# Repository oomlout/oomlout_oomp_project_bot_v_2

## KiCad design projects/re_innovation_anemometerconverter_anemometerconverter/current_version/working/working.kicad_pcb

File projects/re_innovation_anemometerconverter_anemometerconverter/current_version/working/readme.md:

# anemometerconverter
 
## summary 
* id: re_innovation_anemometerconverter_anemometerconverter
* user: re_innovation
* name: anemometerconverter
* board: anemometerconverter
* repo: https://github.com/re-innovation/AnemometerConverter
* src_file_repo_kicad_pcb: AnemometerConverter_PCB/AnemometerConverter.kicad_pcb
* src_file_repo_kicad_pcb_link: https://github.com/re-innovation/AnemometerConverter/tree/master/AnemometerConverter_PCB/AnemometerConverter.kicad_pcb

* src_file_repo_sch: AnemometerConverter_PCB/AnemometerConverter.sch
* src_file_repo_sch_link: https://github.com/re-innovation/AnemometerConverter/tree/master/AnemometerConverter_PCB/AnemometerConverter.sch
* full details link: https://github.com/oomlout/oomlout_oomp_project_bot_v_2/tree/main/projects/re_innovation_anemometerconverter_anemometerconverter/current_version/working

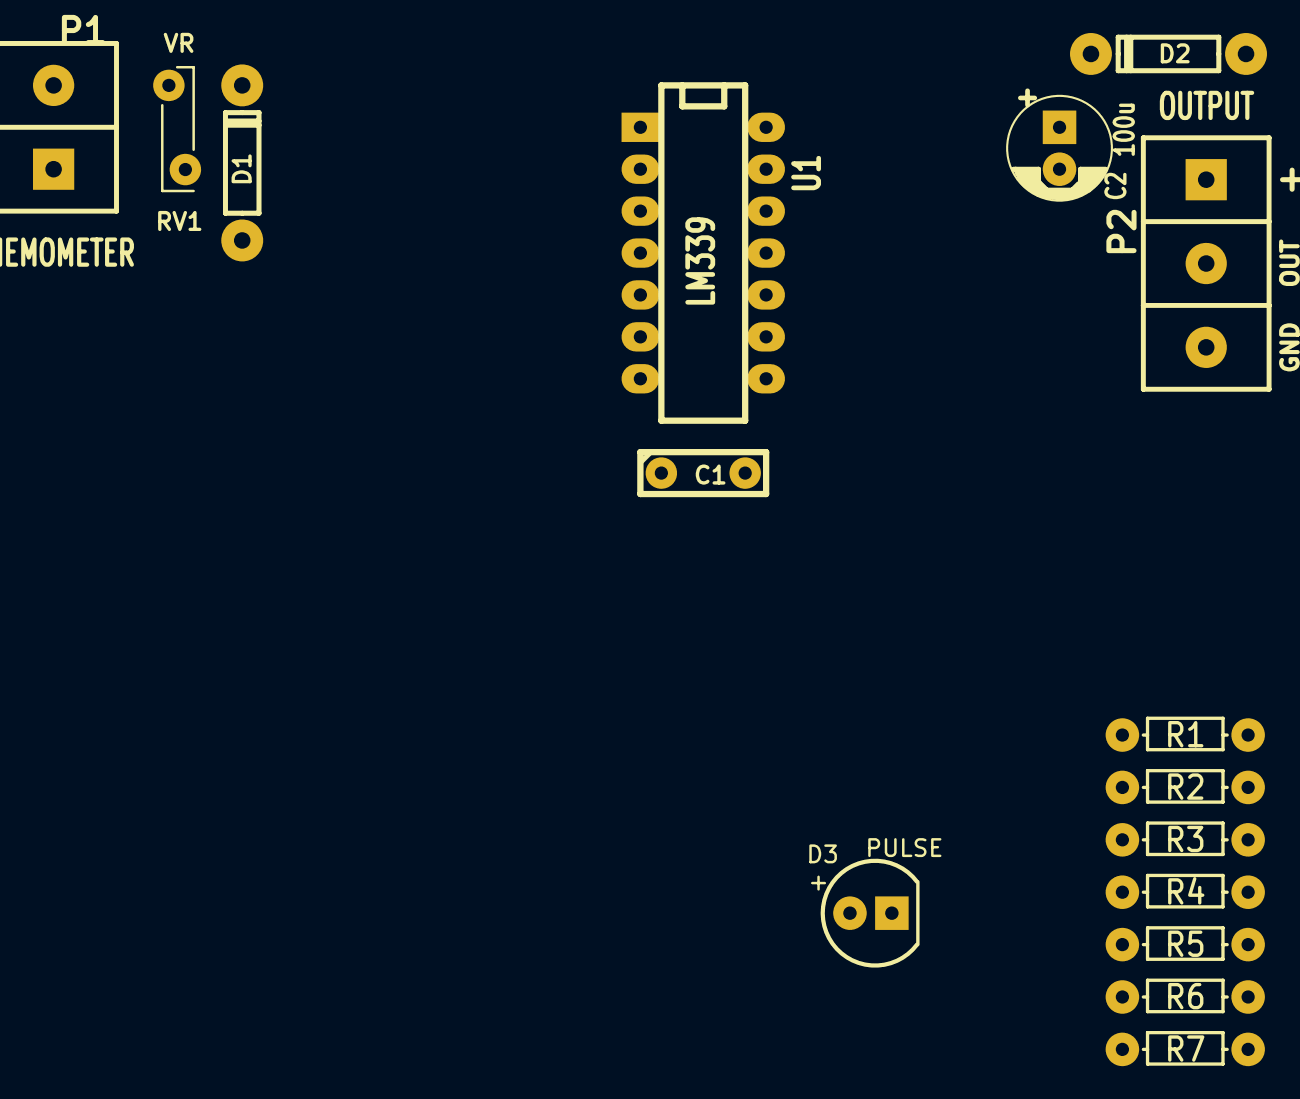
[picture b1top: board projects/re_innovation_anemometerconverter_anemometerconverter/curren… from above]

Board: 2 copper layers, 16 parts (0 on the bottom side), 9 nets, no tracks yet.

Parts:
C1: 22n; C1_wide_lg_pad
C2: 100u; C_1V7_TH
D1: 1N914; TH_Diode_1
D2: 1N4001; TH_Diode_1
D3: PULSE; TH_LED-5MM_larg_pad
P1: ANEMOMETER; SIL-2_screw_terminal
P2: OUTPUT; SIL-3_screw_terminal
R1, R2: 4k7; TH_Resistor_1
R3, R4: 100k; TH_Resistor_1
R5: 10k; TH_Resistor_1
R6: 4M7; TH_Resistor_1
R7: 1k; TH_Resistor_1
RV1: VR; TH_MC36188_FUSE
U1: LM339; DIP-14__300_ELL_lg_pad

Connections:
GND: C1.2, C2.2, D1.2, P1.1, P2.3, R5.2, R7.2, RV1.2, U1.12
unnamed: C1.1, R2.1, R3.2, U1.4
unnamed: D1.1, R1.1, R2.2
unnamed: D2.2, P2.1
unnamed: D3.1, R7.1
unnamed: D3.2, P2.2, R6.1, U1.2
unnamed: P1.2, R1.2, RV1.1
unnamed: R4.2, R5.1, R6.2, U1.5
VCC: C2.1, D2.1, R3.1, R4.1, U1.3

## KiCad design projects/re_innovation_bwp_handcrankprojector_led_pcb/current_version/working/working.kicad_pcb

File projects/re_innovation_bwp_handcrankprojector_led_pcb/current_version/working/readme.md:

# bwp
 
## summary 
* id: re_innovation_bwp_handcrankprojector_led_pcb
* user: re_innovation
* name: bwp
* board: handcrankprojector_led_pcb
* repo: https://github.com/re-innovation/bwp
* src_file_repo_kicad_pcb: Projection_Unit_PCB/LED_Unit_PCB/HandCrankProjector_LED_PCB.kicad_pcb
* src_file_repo_kicad_pcb_link: https://github.com/re-innovation/bwp/tree/master/Projection_Unit_PCB/LED_Unit_PCB/HandCrankProjector_LED_PCB.kicad_pcb

* src_file_repo_sch: Projection_Unit_PCB/LED_Unit_PCB/HandCrankProjector_LED_PCB.sch
* src_file_repo_sch_link: https://github.com/re-innovation/bwp/tree/master/Projection_Unit_PCB/LED_Unit_PCB/HandCrankProjector_LED_PCB.sch
* full details link: https://github.com/oomlout/oomlout_oomp_project_bot_v_2/tree/main/projects/re_innovation_bwp_handcrankprojector_led_pcb/current_version/working

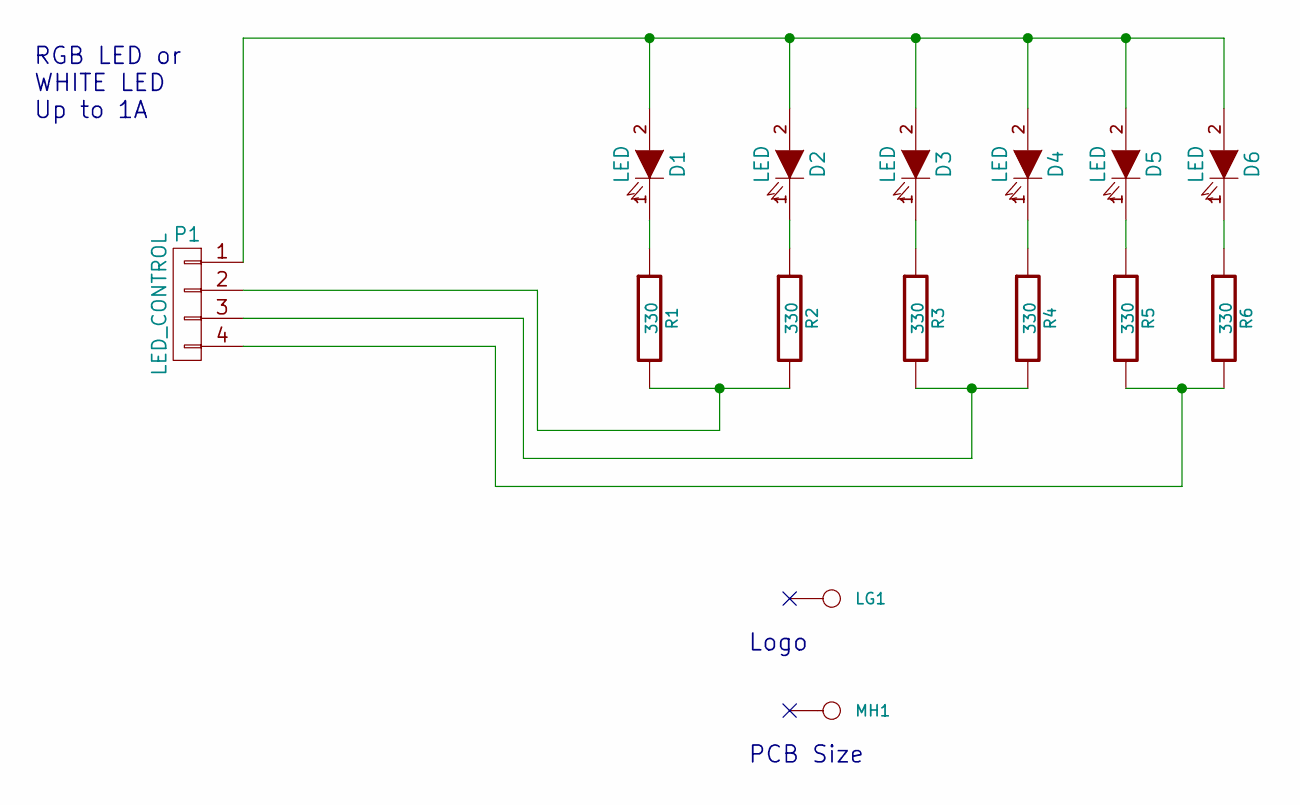
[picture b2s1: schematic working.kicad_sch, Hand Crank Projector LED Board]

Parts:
D1, D2, D3, D4, D5, D6: LED; TH_LED-5MM_larg_pad; Manufacturer Part No Value
LG1: CONN_1; reinnovation_logo_15mm
MH1: CONN_1; PCB_50x50mm
P1: LED_CONTROL; SIL-4_Grove_SCREW
R1, R2, R3, R4, R5, R6: 330; TH_Resistor_1; Manufacturer Part No Value

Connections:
unnamed: D1.1 (K), R1.1
unnamed: D1.2 (A), D2.2 (A), D3.2 (A), D4.2 (A), D5.2 (A), D6.2 (A), P1.1
unnamed: D2.1 (K), R2.1
unnamed: D3.1 (K), R3.1
unnamed: D4.1 (K), R4.1
unnamed: D5.1 (K), R5.1
unnamed: D6.1 (K), R6.1
unnamed: P1.2, R1.2, R2.2
unnamed: P1.3, R3.2, R4.2
unnamed: P1.4, R5.2, R6.2

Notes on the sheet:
PCB Size
RGB LED or WHITE LED Up to 1A
Logo

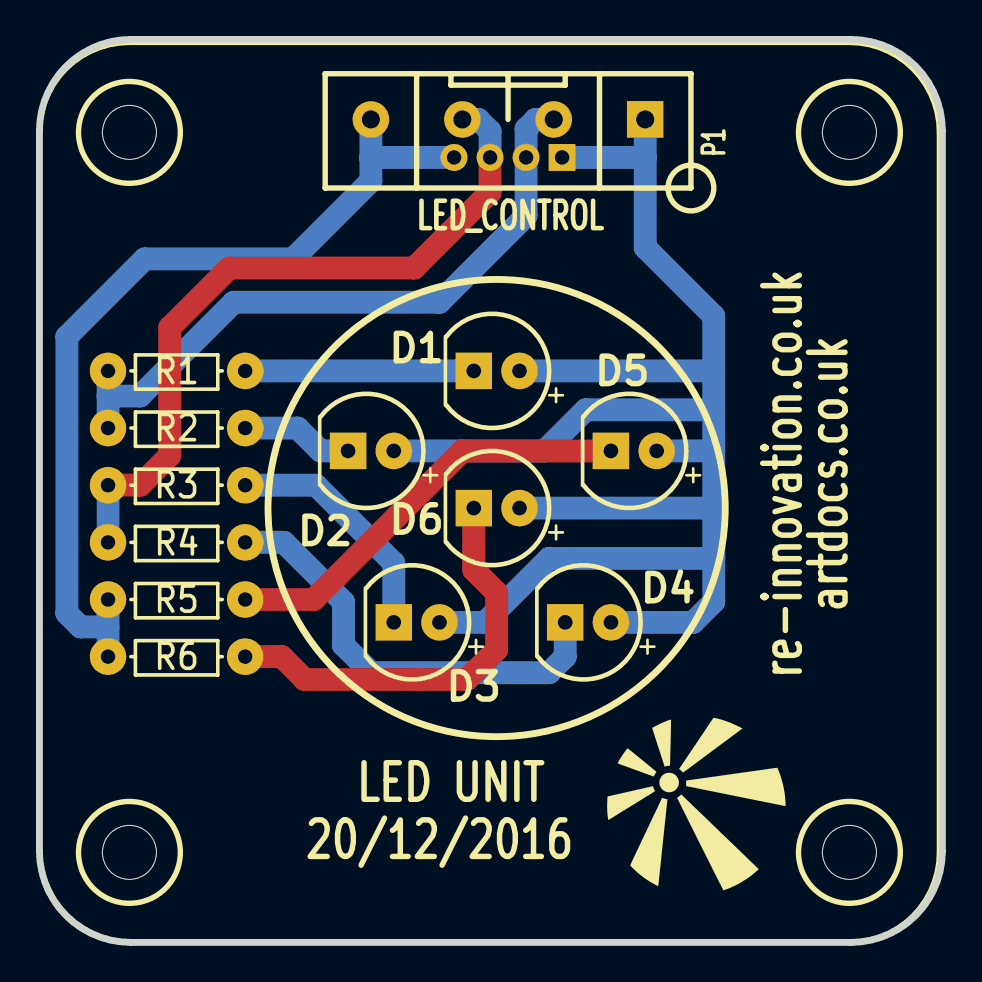
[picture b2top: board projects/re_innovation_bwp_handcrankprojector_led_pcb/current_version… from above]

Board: 2 copper layers, 50.2 x 50.2 mm, 15 parts (0 on the bottom side), 10 nets.

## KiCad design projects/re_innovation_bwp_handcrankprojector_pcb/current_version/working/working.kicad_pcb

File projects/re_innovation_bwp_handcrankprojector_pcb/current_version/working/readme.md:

# bwp
 
## summary 
* id: re_innovation_bwp_handcrankprojector_pcb
* user: re_innovation
* name: bwp
* board: handcrankprojector_pcb
* repo: https://github.com/re-innovation/bwp
* src_file_repo_kicad_pcb: Projection_Unit_PCB/HandCrankProjector_PCB/HandCrankProjector_PCB.kicad_pcb
* src_file_repo_kicad_pcb_link: https://github.com/re-innovation/bwp/tree/master/Projection_Unit_PCB/HandCrankProjector_PCB/HandCrankProjector_PCB.kicad_pcb

* src_file_repo_sch: Projection_Unit_PCB/HandCrankProjector_PCB/HandCrankProjector_PCB.sch
* src_file_repo_sch_link: https://github.com/re-innovation/bwp/tree/master/Projection_Unit_PCB/HandCrankProjector_PCB/HandCrankProjector_PCB.sch
* full details link: https://github.com/oomlout/oomlout_oomp_project_bot_v_2/tree/main/projects/re_innovation_bwp_handcrankprojector_pcb/current_version/working

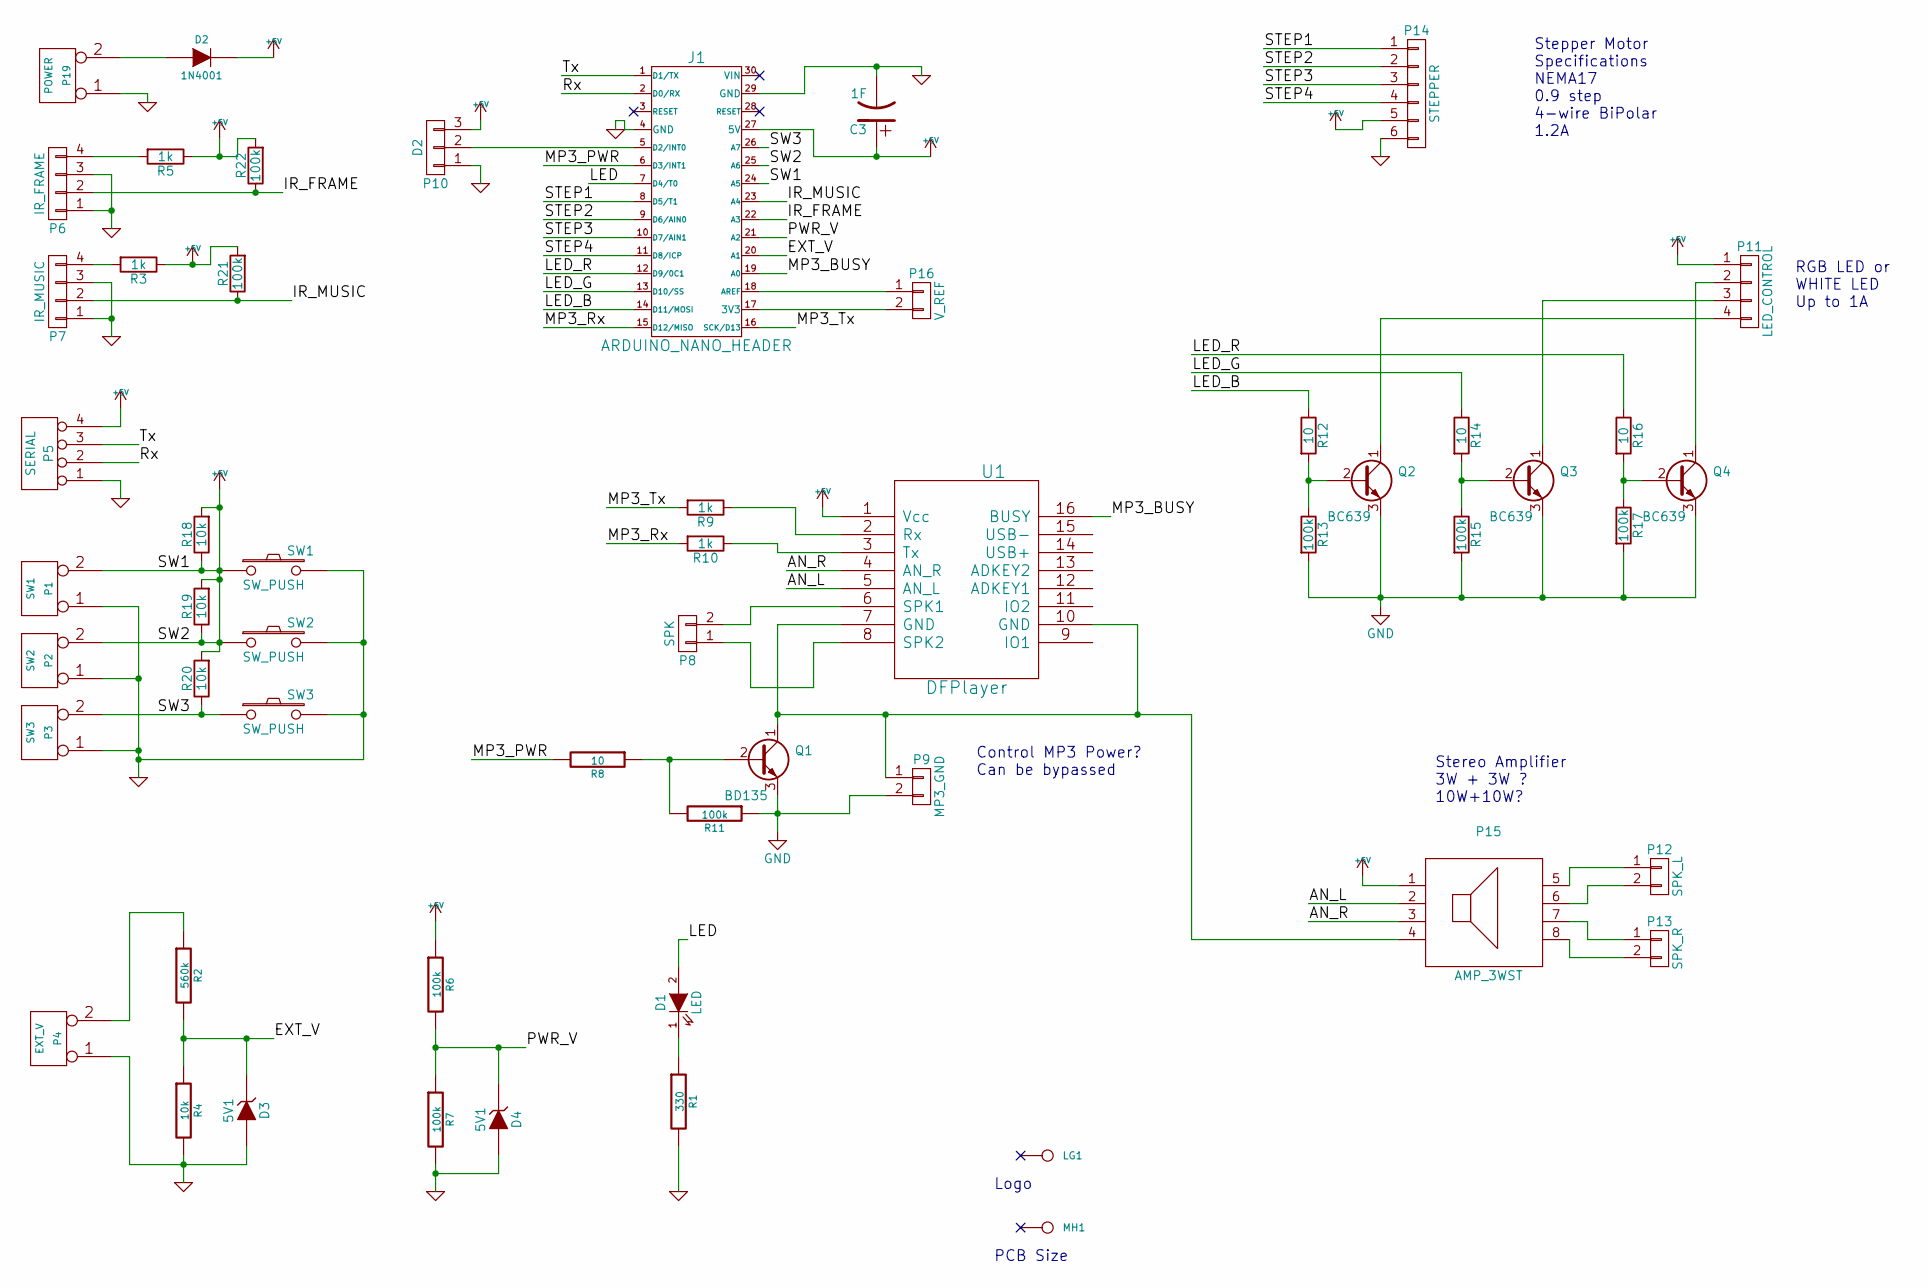
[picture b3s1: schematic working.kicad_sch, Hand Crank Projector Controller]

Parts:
C3: 1F; C_1F_SuperCap; Manufacturer Part No Value
D1: LED; TH_LED-5MM_larg_pad
D2: 1N4001; TH_Diode_1
D3, D4: 5V1; TH_Diode_1
J1: ARDUINO_NANO_HEADER; NANO_DIP_30_600
LG1: CONN_1; reinnovation_logo_15mm
MH1: CONN_1; PCB_75x100mm
P1: SW1; SIL-2_large_hole
P2: SW2; SIL-2_large_hole
P3: SW3; SIL-2_large_hole
P4: EXT_V; SIL-2_screw_terminal
P5: SERIAL; SIL-4_Grove_SIL
P6: IR_FRAME; SIL-4_Grove_SIL
P7: IR_MUSIC; SIL-4_Grove_SIL
P8: SPK; SIL-2_screw_terminal
P9: MP3_GND; SM_2_SLDR_JMP
P10: D2; Pin_Header_Straight_1x03
P11: LED_CONTROL; SIL-4_Grove_SCREW
P12: SPK_L; SIL-2_screw_terminal
P13: SPK_R; SIL-2_screw_terminal
P14: STEPPER; TH_6W_SCREW_TERM
P15: AMP_3WST; TH_PAM8403_Amp
P16: V_REF; SM_2_SLDR_JMP
P19: POWER; SIL-2_screw_terminal; Manufacturer Part No Value
Q1: BD135; TO92-ECB_large_pad_BC639
Q2, Q3, Q4: BC639; TO92-ECB_large_pad_BC639
R1: 330; TH_Resistor_1; Manufacturer Part No Value
R2: 560k; TH_Resistor_1; Manufacturer Part No Value
R3, R5, R9, R10: 1k; TH_Resistor_1
R4: 10k; TH_Resistor_1; Manufacturer Part No Value
R6, R7, R11: 100k; TH_Resistor_1; Manufacturer Part No Value
R8: 10; TH_Resistor_1; Manufacturer Part No Value
R12, R14, R16: 10; TH_Resistor_1
R13, R15, R17, R21, R22: 100k; TH_Resistor_1
R18, R19, R20: 10k; TH_Resistor_1
SW1, SW2, SW3: SW_PUSH; SW_PUSH_single_pins
U1: DFPlayer; TH_DFPlayer_Mini

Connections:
/AN_L: P15.2, U1.5 (AN_L)
/AN_R: P15.3, U1.4 (AN_R)
/EXT_V: D3.2 (K), J1.20 (A1), R2.2, R4.1
/IR_FRAME: J1.22 (A3), P6.2, R22.1
/IR_MUSIC: J1.23 (A4), P7.2, R21.1
/LED: D1.2 (A), J1.7 (D4/T0)
/LED_B: J1.14 (D11/MOSI), R12.1
/LED_G: J1.13 (D10/SS), R14.1
/LED_R: J1.12 (D9/0C1), R16.1
/MP3_BUSY: J1.19 (A0), U1.16 (BUSY)
/MP3_PWR: J1.6 (D3/INT1), R8.2
/MP3_Rx: J1.15 (D12/MISO), R10.2
/MP3_Tx: J1.16 (SCK/D13), R9.2
/PWR_V: D4.2 (K), J1.21 (A2), R6.2, R7.1
/Rx: J1.2 (D0/RX), P5.2
/STEP1: J1.8 (D5/T1), P14.1
/STEP2: J1.9 (D6/AIN0), P14.2
/STEP3: J1.10 (D7/AIN1), P14.3
/STEP4: J1.11 (D8/ICP), P14.4
/SW3: J1.26 (A7), P3.2 (PM), R20.1, SW3.1
/Tx: J1.1 (D1/TX), P5.3
GND: C3.2, D3.1 (A), D4.1 (A), J1.4 (GND), J1.29 (GND), P1.1, P2.1, P3.1, P4.1, P5.1, P6.1, P6.3, P7.1, P7.3, P9.2, P10.1, P14.6, P19.1, Q1.3 (E), Q2.3 (E), Q3.3 (E), Q4.3 (E), R1.2, R4.2, R7.2, R11.1, R13.2, R15.2, R17.2, SW1.2, SW2.2, SW3.2
unnamed: D1.1 (K), R1.1
unnamed: D2.1 (A), P19.2 (PM)
unnamed: J1.5 (D2/INT0), P10.2
unnamed: J1.17 (3V3), P16.2
unnamed: J1.18 (AREF), P16.1
unnamed: P4.2 (PM), R2.1
unnamed: P6.4, R5.2
unnamed: P7.4, R3.2
unnamed: P8.1, U1.8 (SPK2)
unnamed: P8.2, U1.6 (SPK1)
unnamed: P11.2, Q4.1 (C)
unnamed: P11.3, Q3.1 (C)
unnamed: P11.4, Q2.1 (C)
unnamed: P12.1, P15.5
unnamed: P12.2, P15.6
unnamed: P13.1, P15.7
unnamed: P13.2, P15.8
unnamed: P9.1, P15.4, Q1.1 (C), U1.7 (GND), U1.10 (GND)
unnamed: Q1.2 (B), R8.1, R11.2
unnamed: Q2.2 (B), R12.2, R13.1
unnamed: Q3.2 (B), R14.2, R15.1
unnamed: Q4.2 (B), R16.2, R17.1
unnamed: R9.1, U1.2 (Rx)
unnamed: R10.1, U1.3 (Tx)

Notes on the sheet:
Stepper Motor Specifications NEMA17 0.9 step 4-wire BiPolar 1.2A
RGB LED or WHITE LED Up to 1A
Stereo Amplifier 3W + 3W ? 10W+10W?
Logo
PCB Size
Control MP3 Power? Can be bypassed

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
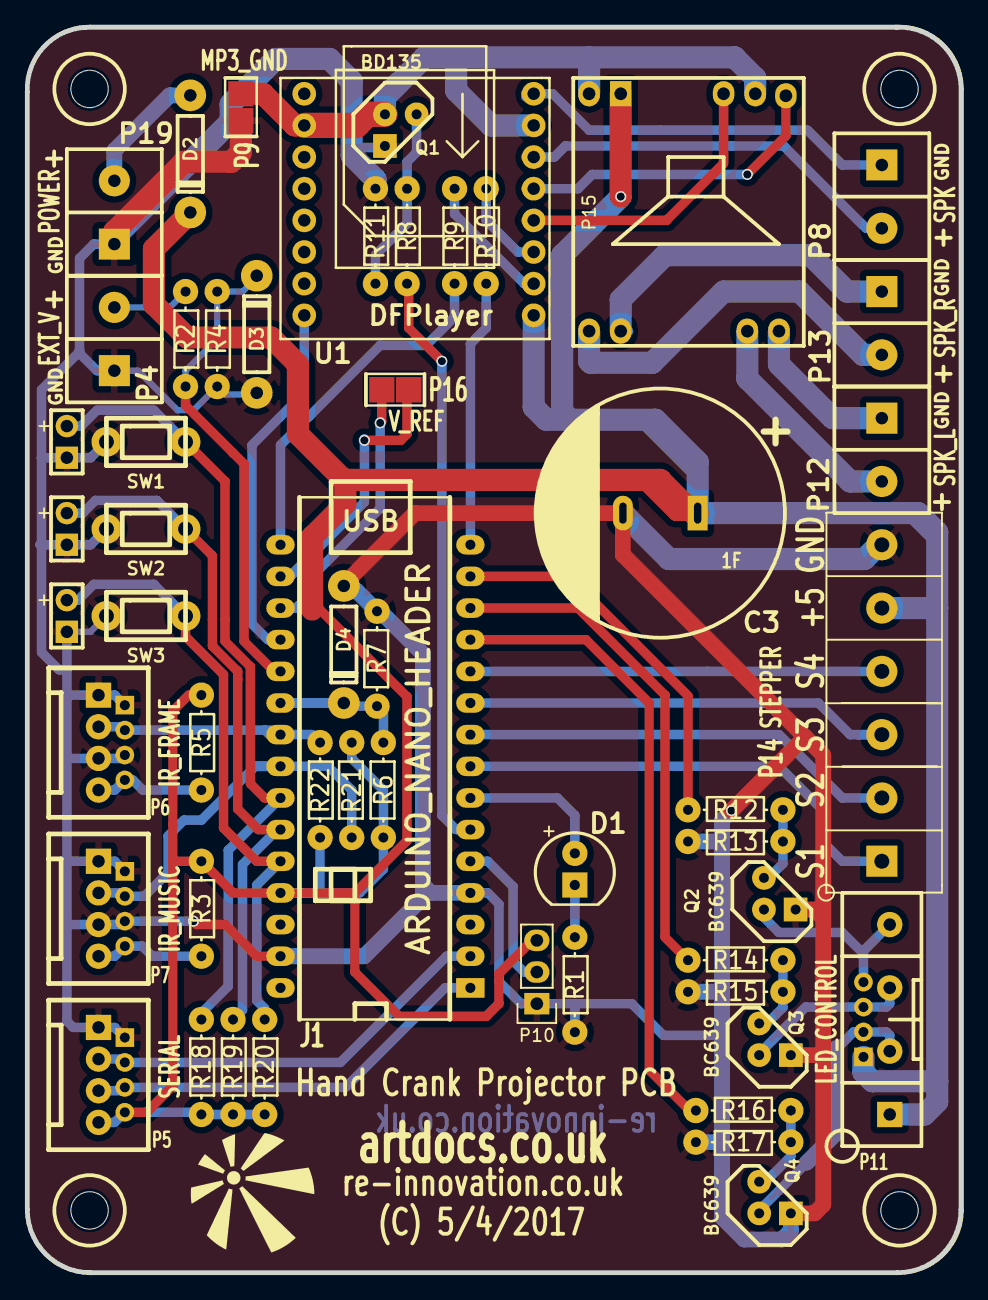
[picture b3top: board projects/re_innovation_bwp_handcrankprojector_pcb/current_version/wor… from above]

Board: 2 copper layers, 74.9 x 99.9 mm, 55 parts (0 on the bottom side), 49 nets.

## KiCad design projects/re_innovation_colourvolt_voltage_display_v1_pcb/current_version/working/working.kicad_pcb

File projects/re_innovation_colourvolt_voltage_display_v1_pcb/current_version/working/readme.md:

# colourvolt
 
## summary 
* id: re_innovation_colourvolt_voltage_display_v1_pcb
* user: re_innovation
* name: colourvolt
* board: voltage_display_v1_pcb
* repo: https://github.com/re-innovation/ColourVolt
* src_file_repo_kicad_pcb: Voltage Display v1 PCB/KiCAD Files/Voltage Display v1 PCB.kicad_pcb
* src_file_repo_kicad_pcb_link: https://github.com/re-innovation/ColourVolt/tree/master/Voltage Display v1 PCB/KiCAD Files/Voltage Display v1 PCB.kicad_pcb

* src_file_repo_sch: Voltage Display v1 PCB/KiCAD Files/Voltage Display v1 PCB.sch
* src_file_repo_sch_link: https://github.com/re-innovation/ColourVolt/tree/master/Voltage Display v1 PCB/KiCAD Files/Voltage Display v1 PCB.sch
* full details link: https://github.com/oomlout/oomlout_oomp_project_bot_v_2/tree/main/projects/re_innovation_colourvolt_voltage_display_v1_pcb/current_version/working

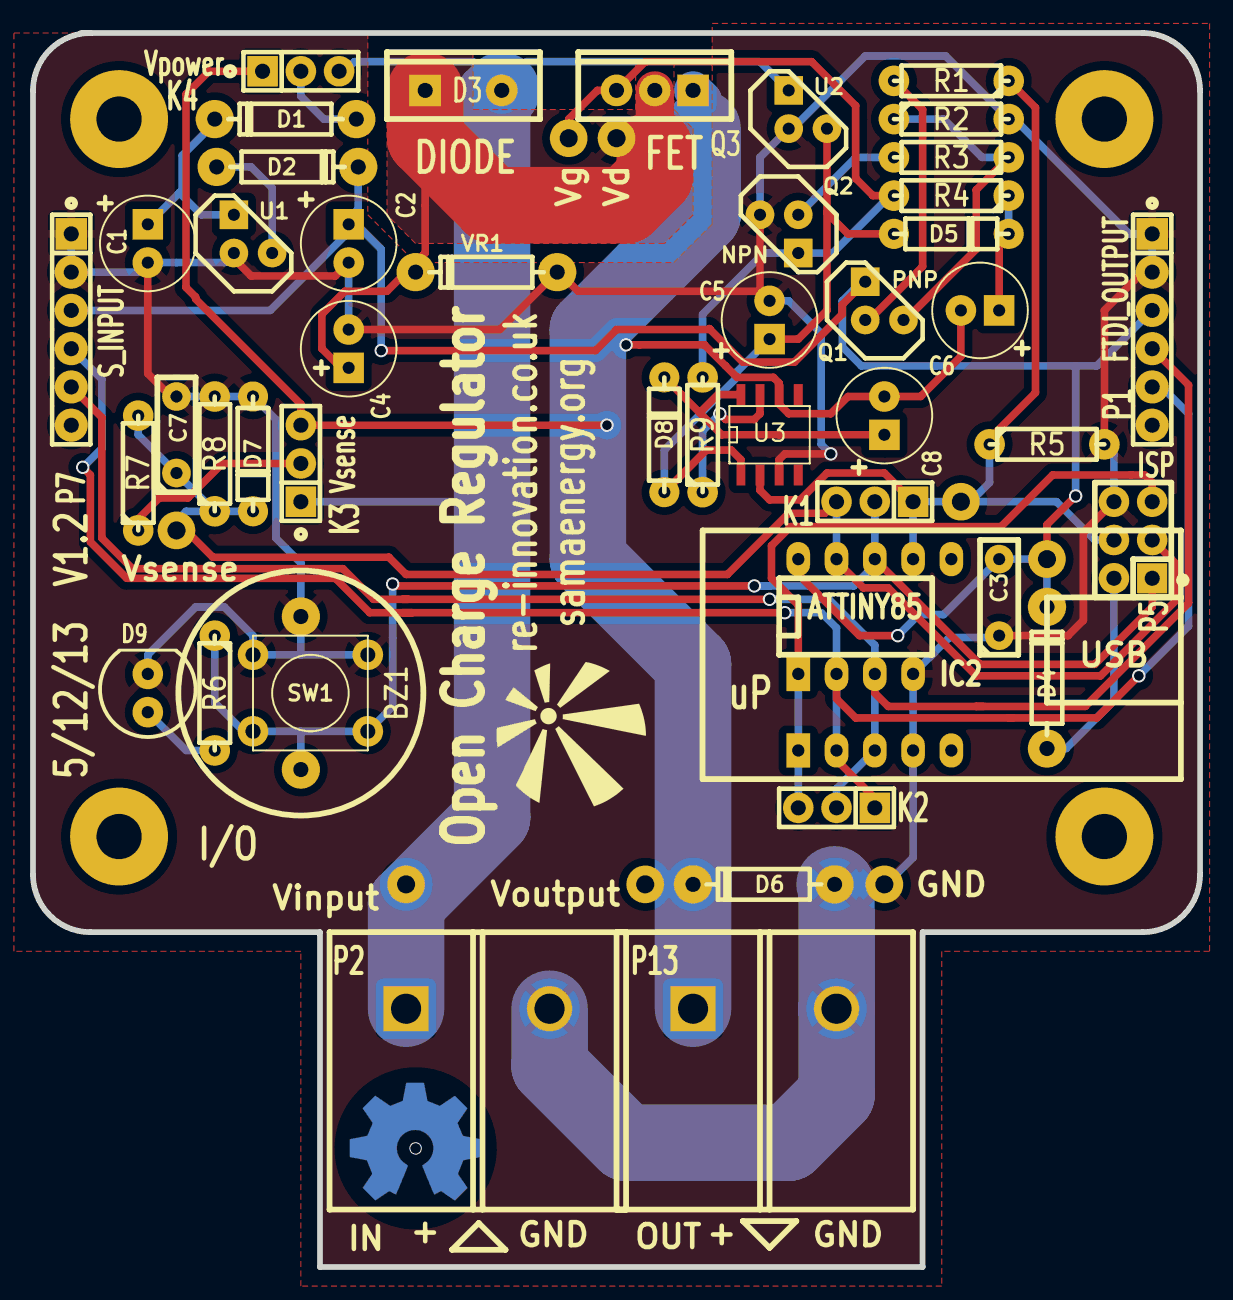
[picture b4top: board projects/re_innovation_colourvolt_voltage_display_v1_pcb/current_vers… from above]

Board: 2 copper layers, 77.5 x 81.9 mm, 59 parts (0 on the bottom side), 25 nets.

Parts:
BZ1: BUZZER; BUZZER_lg_pads
C1: 10uf; C1V7_lg_pad
C2: 100u; C1V7_lg_pad
C3, C7: 100n; C1_wide_lg_pad
C4, C5, C6: 10u; C1V7_lg_pad
C8: CP1; C1V7_lg_pad
D1, D2, D4: 1N4001; D4_lg_pad
D3: VT2045BP; TO220_DIODE
D5: 1N4148; D3_lg_pad
D6: UF4001; D4_lg_pad
D7: 5v1; D3_lg_pad
D8: DIODE; D3_lg_pad
D9: GRN_LED; LED-5MM_larg_pad
IC2: ATTINY85; TRINKET
K1: IO_0-2; SIL-3_lg_pad_1mm
K2: IO_3-5; SIL-3_lg_pad_1mm
K3: Vsense; SIL-3_lg_pad_1mm_marker
K4: Vpower; SIL-3_lg_pad_1mm_marker
MH1, MH2, MH3, MH4: CONN_1; 1pin_3mmhole
P1: FTDI_OUTPUT; SIL-6_large_pads_marker
P2: IN; SIL_2_screw_blocks
P3: Vinput; 1pin_1.2mm
P4: 5V; 1pin_1.2mm
P5: ISP; DIL_3x2_large_pads_1mm
P6: GND; 1pin_1.2mm
P7: S_INPUT; SIL-6_large_pads_marker
P8: Vd; 1pin_1.2mm
P9: Vg; 1pin_1.2mm
P11: Voutput; 1pin_1.2mm
P12: Vsense; 1pin_1.2mm
P13: OUT; SIL_2_screw_blocks
P14: FET_IN; 1pin_1.2mm
Q1: PNP; TO92-EBC_large_pad
Q2: NPN; TO92-EBC_large_pad
Q3: MOSFET_N; TO220_VERT_BUZ11_matt
R1, R4: 1k; R3-LARGE_PADS_0_8_hole
R2: 100k; R3-LARGE_PADS_0_8_hole
R3, R5: 10k; R3-LARGE_PADS_0_8_hole
R6: 330; R3-LARGE_PADS_0_8_hole
R7, R8: R; R3-LARGE_PADS_0_8_hole
R9: 10; R3-LARGE_PADS_0_8_hole
SW1: SW_PUSH; SW_PUSH_SMALL_ml_large_hole
U1: 7805/LM2931; TO92_7805_matt
U2: LM7812; TO92_7805_matt
U3: AUIRS2124; SO8E
VAL: OSHW_logo_small_back
VAL#2: reinnovation_logo_15mm
VR1: P6KE33CA-E3; D4_lg_pad

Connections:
+5V: C2.1, C3.2, D2.2, D4.2, IC2.8, P1.3, P4.1, P7.3, Q1.3
FET: IC2.5, K1.1, P5.4, P14.1, R1.1, R5.1, U3.2
GND: BZ1.2, C1.2, C2.2, C3.1, C4.2, C5.2, C7.2, D6.1, D7.1, D9.2, IC2.4, P1.1, P1.2, P2.2, P5.6, P6.1, P7.1, P7.2, P13.2, Q2.1, R2.2, R5.2, R8.2, SW1.2, U1.GND, U2.GND, U3.3, VR1.1
LED: BZ1.1, IC2.6, K1.2, P5.1, R6.1, SW1.1
unnamed: D9.1, R6.2
unnamed: K3.2, R7.1
unnamed: Q2.2, R3.2
unnamed: Q1.2, R1.2
unnamed: D4.1, P5.2
unnamed: D1.1, K4.2
unnamed: C8.1, D8.2, U3.8
unnamed: R9.1, U3.7
unnamed: C1.1, D1.2, U1.VI
unnamed: C6.1, D5.2, R4.1
unnamed: P9.1, Q2.3, Q3.G, R4.2, R9.2
unnamed: C4.1, D3.1, P8.1, Q3.D, VR1.2
unnamed: Q1.1, R2.1, R3.1
unnamed: D2.1, U1.VO
unnamed: C5.1, D5.1, D8.1, U2.VO, U3.1
RESET: IC2.1, K2.3, P5.5
Rx: IC2.3, K2.2, P1.4, P7.5
SCK: C7.1, D7.2, IC2.7, K1.3, P5.3, P12.1, R7.2, R8.1
Tx: IC2.2, K2.1, P1.5, P7.4
Vinput: D3.2, K3.1, K4.3, P2.1, P3.1, U2.VI
Voutput: C6.2, C8.2, D6.2, K3.3, K4.1, P11.1, P13.1, Q3.S, U3.6

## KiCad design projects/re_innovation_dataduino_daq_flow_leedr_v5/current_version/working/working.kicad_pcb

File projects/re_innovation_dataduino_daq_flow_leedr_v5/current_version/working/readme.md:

# dataduino
 
## summary 
* id: re_innovation_dataduino_daq_flow_leedr_v5
* user: re_innovation
* name: dataduino
* board: daq_flow_leedr_v5
* repo: https://github.com/re-innovation/DataDuino
* src_file_repo_kicad_pcb: DataDuino_PCB/DAQ_Flow_LEEDR_v5.kicad_pcb
* src_file_repo_kicad_pcb_link: https://github.com/re-innovation/DataDuino/tree/master/DataDuino_PCB/DAQ_Flow_LEEDR_v5.kicad_pcb

* src_file_repo_sch: DataDuino_PCB/DAQ_Flow_LEEDR_v5.sch
* src_file_repo_sch_link: https://github.com/re-innovation/DataDuino/tree/master/DataDuino_PCB/DAQ_Flow_LEEDR_v5.sch
* full details link: https://github.com/oomlout/oomlout_oomp_project_bot_v_2/tree/main/projects/re_innovation_dataduino_daq_flow_leedr_v5/current_version/working

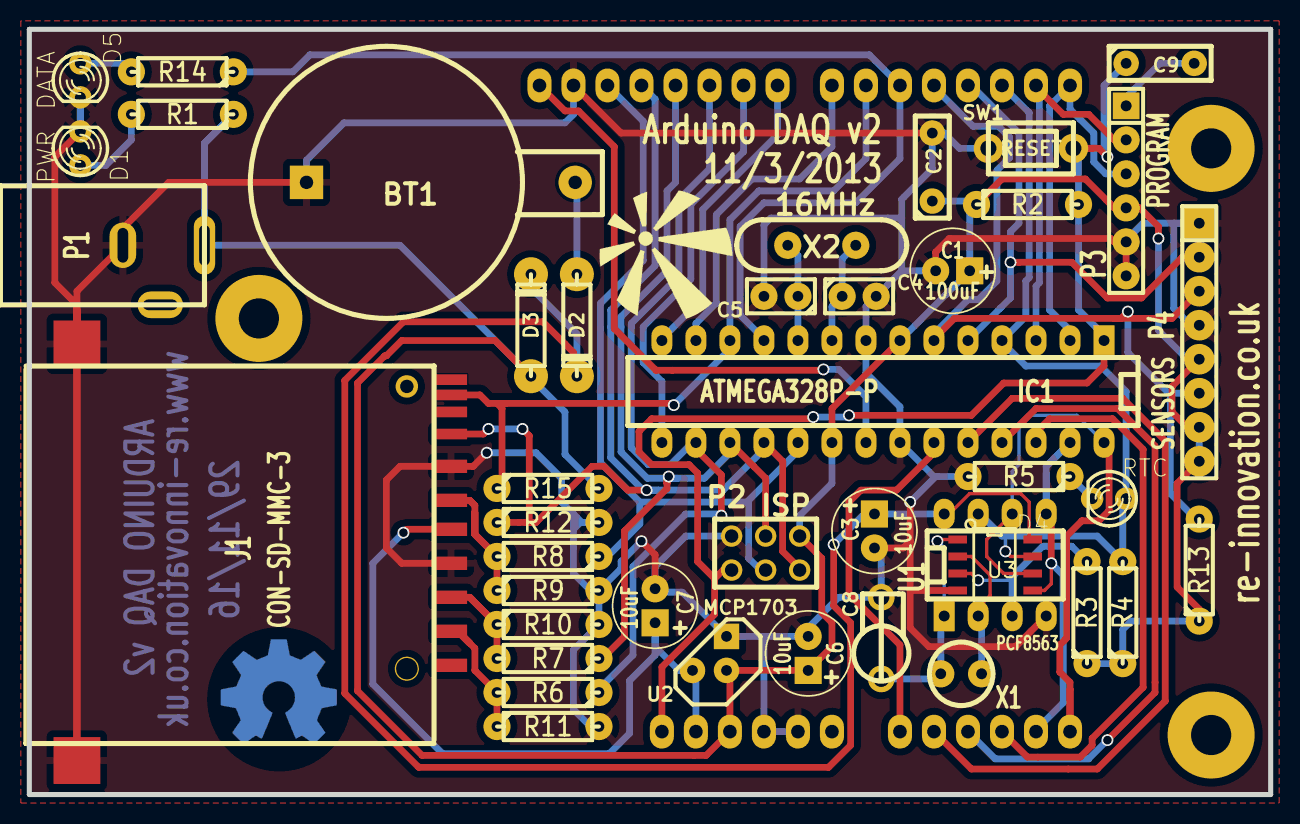
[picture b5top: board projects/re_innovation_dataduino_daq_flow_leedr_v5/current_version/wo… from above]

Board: 2 copper layers, 92.7 x 57.1 mm, 48 parts (0 on the bottom side), 39 nets.

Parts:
BT1: CR2032 3V BATT; Batt_conn_20mm_thruh
C1: 100uF; C1V7_lg_pad_lg_hole
C2: 100nF; C1_wide_lg_pad_2
C3, C6, C7: 10uF; C1V7_lg_pad_lg_hole
C4, C5: 22pF; C1_lg_pad
C8: CTRIM; CTrim
C9: 100nF; C1_wide_lg_pad
D1: PWR; led-LED3MM_matt
D2, D3: 1N4148; D3_lg_pad
D4: RTC; led-LED3MM_matt
D5: DATA; led-LED3MM_matt
IC1: ATMEGA328P-P; DIP-28__300_ELL
J1: CON-SD-MMC-3; SD_holder_3M_matt
P1: POWER; DC_Power_2_1
P2: ISP; ISP_3x2
P3: PROGRAM; SIL-6_large_pads
P4: SENSORS; SIL-8_lg_pad_2
P6, P7, P8: CONN_1; 1pin_3mmhole
R1, R14: 1k; R3-LARGE_PADS_0_8_hole
R2, R3, R4, R15: 10k; R3-LARGE_PADS_0_8_hole
R5: 330; R3-LARGE_PADS_0_8_hole
R6, R7, R8: 2k2; R3-LARGE_PADS_0_8_hole
R9, R10, R11: 3k3; R3-LARGE_PADS_0_8_hole
R12: 100k; R3-LARGE_PADS_0_8_hole
R13: 4k7; R3-LARGE_PADS_0_8_hole
SHIELD1: ARDUINO_SHIELD; ARDUINO_SHIELD_040pins_no_hole_large_pad_no_outline
SW1: RESET; SW_PUSH_single_pins
U1: PCF8563; DIP-8__300_ELL
U2: MCP1703; TO92_MC1703_matt
U3: PCF8563; SM_SOIC_8
VAL: OSHW_logo_small_back
VAL#2: reinnovation_logo_15mm
X1: 32.27 kHz; Xtal_watch_matt
X2: 16MHz; Xtal_small_matt

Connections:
3v3: C7.1, J1.4, SHIELD1.3V3, U2.VO
+5V: C1.1, C2.1, C6.1, D3.1, IC1.7, IC1.20, P1.2, P2.2, P3.4, P4.5, P4.7, P4.8, R1.1, R2.1, R3.1, R4.1, R13.1, R15.2, SHIELD1.5V, U2.VI
/a0: IC1.23, SHIELD1.AD0
/a1: IC1.24, SHIELD1.AD1
/a2: IC1.25, SHIELD1.AD2
/a3: IC1.26, SHIELD1.AD3
/d7: IC1.13, SHIELD1.7
/d8: IC1.14, SHIELD1.8
/d9: IC1.15, SHIELD1.9
A4: IC1.27, SHIELD1.AD4, U1.5, U3.5
A5: IC1.28, SHIELD1.AD5, U1.6, U3.6
CD: IC1.12, J1.CD, R15.1, SHIELD1.6
D2: D4.1, IC1.4, R4.2, SHIELD1.2, U1.7, U3.7
D3: IC1.5, P4.2, SHIELD1.3
D4: IC1.6, P4.3, P4.6, R13.2, SHIELD1.4
D5: IC1.11, R14.1, SHIELD1.5
D10: IC1.16, R6.1, SHIELD1.10
D11: IC1.17, P2.4, R7.1, SHIELD1.11
D12: IC1.18, J1.7, P2.1, R12.1, SHIELD1.12
D13: IC1.19, P2.3, R8.1, SHIELD1.13
GND: BT1.2, C1.2, C2.2, C3.2, C4.2, C5.2, C6.2, C7.2, C8.2, D1.2, D5.2, IC1.8, IC1.22, J1.3, J1.6, P1.1, P2.6, P3.5, P3.6, P4.1, P4.4, R5.2, R9.2, R10.2, R11.2, R12.2, SHIELD1.GND1, SHIELD1.GND2, SHIELD1.GND3, SW1.2, U1.4, U2.GND, U3.4
unnamed: BT1.1, D2.1
unnamed: C3.1, D2.2, D3.2, U1.8, U3.8
unnamed: C4.1, IC1.9, X2.1
unnamed: C5.1, IC1.10, X2.3
unnamed: C8.1, U1.1, U3.1, X1.3
unnamed: C9.2, P3.1
unnamed: D1.1, R1.2
unnamed: D4.2, R5.1
unnamed: D5.1, R14.2
unnamed: IC1.21, SHIELD1.AREF
unnamed: J1.1, R6.2, R11.1
unnamed: J1.2, R7.2, R10.1
unnamed: J1.5, R8.2, R9.1
unnamed: R3.2, U1.3, U3.3
unnamed: U1.2, U3.2, X1.1
RESET: C9.1, IC1.1, P2.5, R2.2, SHIELD1.RST, SW1.1
RxD: IC1.2, P3.3, SHIELD1.0
TxD: IC1.3, P3.2, SHIELD1.1

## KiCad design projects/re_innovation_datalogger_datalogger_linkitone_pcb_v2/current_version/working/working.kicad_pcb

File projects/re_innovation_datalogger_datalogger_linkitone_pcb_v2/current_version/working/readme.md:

# datalogger
 
## summary 
* id: re_innovation_datalogger_datalogger_linkitone_pcb_v2
* user: re_innovation
* name: datalogger
* board: datalogger_linkitone_pcb_v2
* repo: https://github.com/re-innovation/DataLogger
* src_file_repo_kicad_pcb: PCB/DataLogger PCB v2/DataLogger_LinkItOne_PCB_v2.kicad_pcb
* src_file_repo_kicad_pcb_link: https://github.com/re-innovation/DataLogger/tree/master/PCB/DataLogger PCB v2/DataLogger_LinkItOne_PCB_v2.kicad_pcb

* src_file_repo_sch: 
* src_file_repo_sch_link: https://github.com/re-innovation/DataLogger/tree/master/
* full details link: https://github.com/oomlout/oomlout_oomp_project_bot_v_2/tree/main/projects/re_innovation_datalogger_datalogger_linkitone_pcb_v2/current_version/working

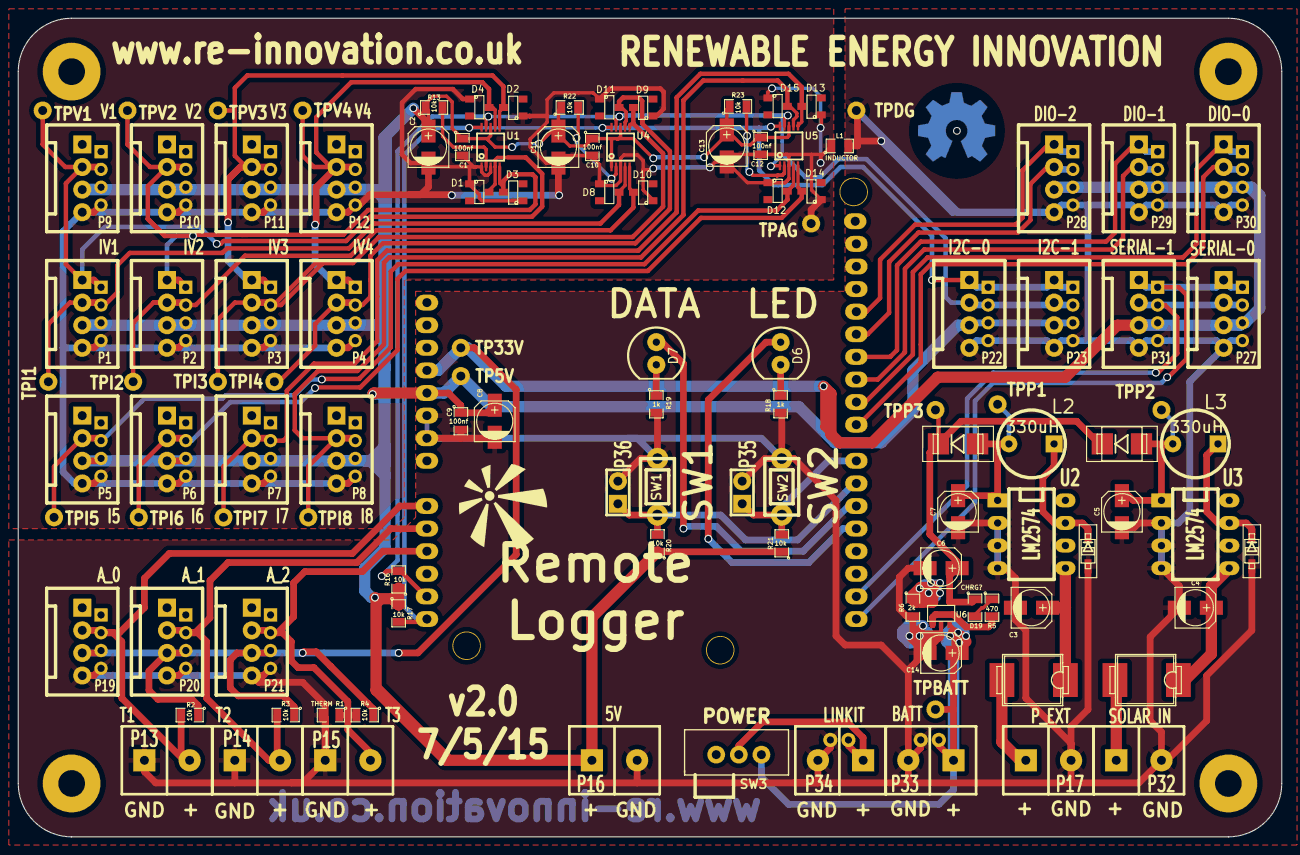
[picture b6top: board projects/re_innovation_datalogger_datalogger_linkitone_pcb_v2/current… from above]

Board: 2 copper layers, 142.0 x 92.0 mm, 121 parts (0 on the bottom side), 52 nets.

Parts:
C1, C9, C10, C12: 100nf; SM0805
C2, C8, C11, C13: 10uf; c_elec_4x5.3
C3, C4: 22uf; c_elec_4x5.3
C5, C7: 220uf; c_elec_4x5.3
C6, C14: 4.7uf; c_elec_4x5.3
D1, D2, D3, D4, D8, D9, D10, D11, D12, D13, D14, D15: ZENER_SOT23; SOT23
D5, D16: 1N5819; SOD123_matt_1N4001
D6: LED; LED-5MM_larg_pad
D7: DATA; LED-5MM_larg_pad
D17, D18: B150; -SMB
D19: CHRG?; SM0805
F1, F2: 1A; -SMC
L1: INDUCTOR; SM0805
L2, L3: 330uH; INDUCTOR_V
P1: IV1; SIL-4_Grove_SIL
P2: IV2; SIL-4_Grove_SIL
P3: IV3; SIL-4_Grove_SIL
P4: IV4; SIL-4_Grove_SIL
P5: I5; SIL-4_Grove_SIL
P6: I6; SIL-4_Grove_SIL
P7: I7; SIL-4_Grove_SIL
P8: I8; SIL-4_Grove_SIL
P9: V1; SIL-4_Grove_SIL
P10: V2; SIL-4_Grove_SIL
P11: V3; SIL-4_Grove_SIL
P12: V4; SIL-4_Grove_SIL
P13: T1; SIL-2_screw_terminal
P14: T2; SIL-2_screw_terminal
P15: T3; SIL-2_screw_terminal
P16: 5V; SIL-2_screw_terminal
P17: P_EXT; SIL-2_screw_terminal
P18, P24, P25, P26: CONN_1; 1pin_3mmhole
P19: A_0; SIL-4_Grove_SIL
P20: A_1; SIL-4_Grove_SIL
P21: A_2; SIL-4_Grove_SIL
P22: I2C-0; SIL-4_Grove_SIL
P23: I2C-1; SIL-4_Grove_SIL
P27: SERIAL-0; SIL-4_Grove_SIL
P28: DIO-2; SIL-4_Grove_SIL
P29: DIO-1; SIL-4_Grove_SIL
P30: DIO-0; SIL-4_Grove_SIL
P31: SERIAL-1; SIL-4_Grove_SIL
P32: SOLAR_IN; SIL-2_screw_terminal
P33: BATT; SIL_2_screw_+_JST_2mm
P34: LINKIT; SIL_2_screw_+_JST_2mm
P35: SW2; SIL-2_lg_pad_1mm
P36: SW1; SIL-2_lg_pad_1mm
P37: TP33V; 1pin_0_8mm
P38: TP5V; 1pin_0_8mm
P39: TPV1; 1pin_0_8mm
P40: TPV3; 1pin_0_8mm
P41: TPV2; 1pin_0_8mm
P42: TPV4; 1pin_0_8mm
P43: TPAG; 1pin_0_8mm
P44: TPP1; 1pin_0_8mm
P45: TPP2; 1pin_0_8mm
P46: TPDG; 1pin_0_8mm
P47: TPP3; 1pin_0_8mm
P48: TPBATT; 1pin_0_8mm
P49: TPI5; 1pin_0_8mm
P50: TPI6; 1pin_0_8mm
P51: TPI7; 1pin_0_8mm
P52: TPI8; 1pin_0_8mm
P53: TPI1; 1pin_0_8mm
P54: TPI2; 1pin_0_8mm
P55: TPI3; 1pin_0_8mm
P56: TPI4; 1pin_0_8mm
R1: THERM; SM0805
R2, R3, R4, R13, R16, R17, R20, R21, R22, R23: 10k; SM0805
R5: 470; SM0805
R6: 2k; SM0805
R18, R19: 1k; SM0805
SHIELD1: LINKITONE_SHIELD; ARDUINO_SHIELD_LinkIt_ONE_no_edge
SW1: SW1; SW_PUSH_single_pins
SW2: SW2; SW_PUSH_single_pins
SW3: POWER; SW_SPDT_rapid_783760
U1, U4, U5: ADS1115; MSOP10-0.5
U2, U3: LM2574; DIP-8__300_ELL
U6: MCP73831; SOT23-5
VAL: reinnovation_logo_15mm
VAL#2: OSHW_logo_small_back

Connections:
+3.3V: P19.3, P20.3, P21.3, P27.3, P28.3, P29.3, P30.3, P31.3, P37.1, R2.1, R3.1, R4.1, SHIELD1.3V3
+5V: C1.1, C2.1, C8.1, C9.1, C10.1, C11.1, C12.1, C13.1, P1.3, P2.3, P3.3, P4.3, P5.3, P6.3, P7.3, P8.3, P9.3, P10.3, P11.3, P12.3, P16.1, P22.3, P23.3, P38.1, R13.1, R16.1, R17.1, R20.1, R21.1, R22.1, R23.1, SHIELD1.5V, U1.8, U4.1, U4.8, U5.8
/DataLoggerCurrentADC1/I1: D8.3, P1.2, P53.1, U4.4
/DataLoggerCurrentADC1/I2: D10.3, P2.2, P54.1, U4.5
/DataLoggerCurrentADC1/I3: D9.3, P3.2, P55.1, U4.6
/DataLoggerCurrentADC1/I4: D11.3, P4.2, P56.1, U4.7
/DataLoggerCurrentADC1/SCLK: P22.1, P23.1, R17.2, SHIELD1.SCL, U1.10, U4.10, U5.10
/DataLoggerCurrentADC1/SDA: P22.2, P23.2, R16.2, SHIELD1.SDA, U1.9, U4.9, U5.1, U5.9
/DataLoggerCurrentADC2/I5: D12.3, P5.2, P49.1, U5.4
/DataLoggerCurrentADC2/I6: D14.3, P6.2, P50.1, U5.5
/DataLoggerCurrentADC2/I7: D13.3, P7.2, P51.1, U5.6
/DataLoggerCurrentADC2/I8: D15.3, P8.2, P52.1, U5.7
/DataLoggerVoltageADC1/V1: D1.3, P1.1, P9.2, P39.1, U1.4
/DataLoggerVoltageADC1/V2: D3.3, P2.1, P10.2, P41.1, U1.5
/DataLoggerVoltageADC1/V3: D2.3, P3.1, P11.2, P40.1, U1.6
/DataLoggerVoltageADC1/V4: D4.3, P4.1, P12.2, P42.1, U1.7
/MicroController/AD0: P13.2, P19.2, R2.2, SHIELD1.AD0
/MicroController/AD1: P14.2, P20.2, R3.2, SHIELD1.AD1
/MicroController/AD2: P15.2, P21.2, R1.1, R4.2, SHIELD1.AD2
/MicroController/DIO0: P30.2, SHIELD1.8
/MicroController/DIO1: P30.1, SHIELD1.9
/MicroController/DIO2: P29.2, SHIELD1.10
/MicroController/DIO3: P29.1, SHIELD1.11
/MicroController/DIO4: P28.2, SHIELD1.12
/MicroController/DIO5: P28.1, SHIELD1.13
/MicroController/Rx: P27.1, P31.1, SHIELD1.0
/MicroController/Tx: P27.2, P31.2, SHIELD1.1
/PowerSupplyUnit/BATT+: C14.1, P33.1, P48.1, SW3.1, U6.3
/PowerSupplyUnit/SOLAR_IN: C4.1, F2.1, U3.5
/PowerSupplyUnit/Vin: C3.1, F1.1, U2.5
AGND: C1.2, C2.2, C10.2, C11.2, C12.2, C13.2, D1.1, D2.1, D3.1, D4.1, D8.1, D9.1, D10.1, D11.1, D12.1, D13.1, D14.1, D15.1, L1.1, P1.4, P2.4, P3.4, P4.4, P5.4, P6.4, P7.4, P8.4, P9.4, P10.4, P11.4, P12.4, P43.1, U1.1, U1.3, U4.3, U5.3
DGND: C3.2, C4.2, C5.2, C6.2, C7.2, C8.2, C9.2, C14.2, D5.1, D16.1, L1.2, P13.1, P14.1, P15.1, P16.2, P17.2, P19.4, P20.4, P21.4, P22.4, P23.4, P27.4, P28.4, P29.4, P30.4, P31.4, P32.2, P33.2, P34.2, P35.2, P36.2, P46.1, R1.2, R6.2, R18.2, R19.2, SHIELD1.GND1, SHIELD1.GND2, SW1.2, SW2.1, U2.2, U2.3, U2.4, U3.2, U3.3, U3.4, U6.2
unnamed: F1.2, P17.1
unnamed: P34.1, SW3.2
unnamed: F2.2, P32.1
unnamed: D6.2, R18.1
unnamed: D7.2, R19.1
unnamed: D6.1, SHIELD1.4
unnamed: D7.1, SHIELD1.5
unnamed: P36.1, R20.2, SHIELD1.6, SW1.1
unnamed: P35.1, R21.2, SHIELD1.7, SW2.2
unnamed: R5.2, U6.1
unnamed: D19.2, R5.1
unnamed: R6.1, U6.5
unnamed: D5.2, L2.1, U2.7
unnamed: C7.1, D17.2, L2.2, P44.1, U2.1
unnamed: C6.1, D17.1, D18.1, D19.1, P47.1, U6.4
unnamed: C5.1, D18.2, L3.2, P45.1, U3.1
unnamed: D16.2, L3.1, U3.7
unnamed: R13.2, U1.2
unnamed: R22.2, U4.2
unnamed: R23.2, U5.2
